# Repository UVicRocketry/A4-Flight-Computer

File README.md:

# Anduril 4 Flight Computer
**Project Charter:** [[[UVR-CH-068] Flight Computer Project Charter]](https://docs.google.com/document/d/1PksAvCCPt7eP-2tlsQyjIq21KkHghG1seeA3lu4UV-o/edit).

## Hardware
Hardware designed in KiCAD. If any footprints are added create a folder with the component name in the component-library folder and export all the files to there. When importing footprints and symbols add them to the A4-Flight-Computer library in KiCAD. Also add any datasheet and relevent documentation to this folder.

## Software
Software is an STM32CubeMX/STM32CubeIDE project using FreeRTOS.
[[Get STM32 software development tools]](https://www.st.com/en/development-tools/stm32-software-development-tools.html)

Unit testing: test infrastructure not set up yet.

### Source organization

The organizational idea is to separate the CubeMX-generated STM32 code from the project-specific application code:

```text
software/A4-Flight-Computer/
├── Core/                         # CubeMX-generated startup and HAL integration
│   ├── Inc/
│   └── Src/
├── App/                          # User-owned flight-computer application
|   ├── Inc/                      # Shared application headers such as config options
|   ├── Src/                      # General application sources such as initialization
│   ├── Services/                 # Services, state machines, etc. shared between tasks
│   ├── Tasks/                    # FreeRTOS task implementations
│   └── Interrupts/               # GPIO/timer/CAN interrupt handlers
├── Drivers/
│   ├── BSP/A4FlightComputer/     # Board-specific hardware abstraction
│   ├── CMSIS/
│   └── STM32H5xx_HAL_Driver/
└── Tests/
    ├── Unit/                     # Google Test unit tests
    └── Mocks/                    # Mock functions for use in unit tests
```

`Core/` should remain mostly as generated by CubeMX. Project-specific application code should be placed in `App/`, hardware interfaces specific to the A4 Flight Computer board
(i.e. accelerometer interface) should be placed in `Drivers/BSP/`, and Google Test cases and mocks should be placed in `Tests/Unit/` and `Tests/Mocks/`.

Handlers in `App/Interrupts/` shall be ISR-safe and perform minimal processing except setting/clearing flags and queuing data to be processed by Tasks. Hardware-independent logic
belongs in `App/Services/` and should not depend directly on STM32 HAL or FreeRTOS.

Unit tests are built on the host with Google Test. Application services
should be testable without STM32 hardware, HAL initialization, or starting the
FreeRTOS scheduler. Use interfaces and fakes for hardware-dependent behavior.

## Setup Guide
*[Fill out if applicable]*

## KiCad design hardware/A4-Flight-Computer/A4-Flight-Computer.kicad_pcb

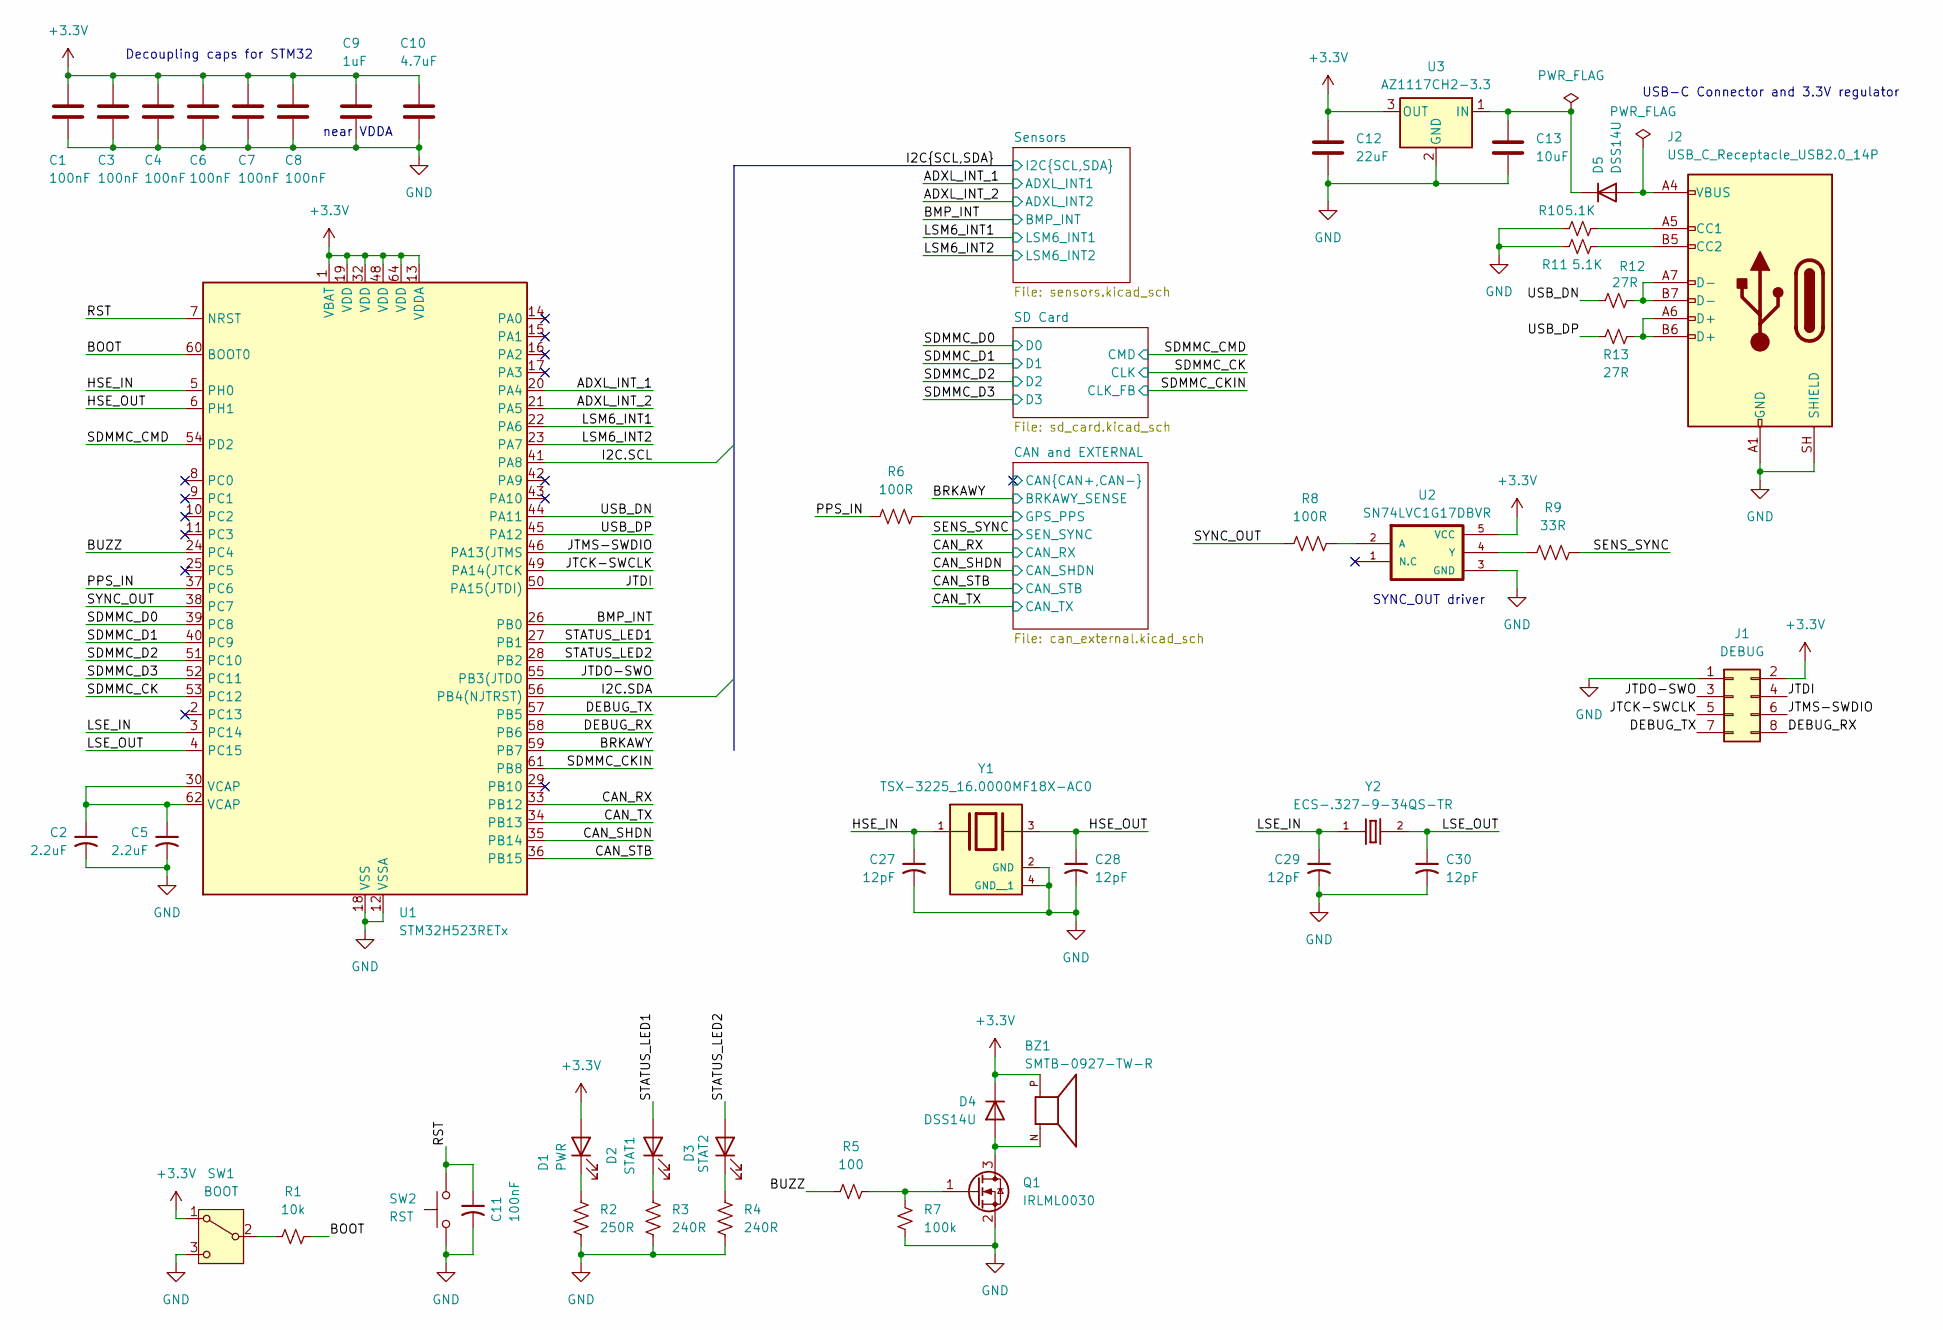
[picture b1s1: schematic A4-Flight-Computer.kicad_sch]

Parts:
BZ1: SMTB-0927-TW-R; XDCR_SMTB-0927-TW-R; MPN SMTB-0927-TW-R
C1, C3, C4, C6, C7, C8, C11: 100nF; C_0402_1005Metric
C2, C5: 2.2uF; C_0402_1005Metric
C9: 1uF; C_0402_1005Metric
C10: 4.7uF; C_0402_1005Metric
C12: 22uF; C_0402_1005Metric
C13: 10uF; C_0402_1005Metric
C27, C28, C29, C30: 12pF; C_0402_1005Metric
D1: PWR; LED_0805_2012Metric
D2: STAT1; LED_0805_2012Metric
D3: STAT2; LED_0805_2012Metric
D4, D5: DSS14U; D_SOD-123
J1: DEBUG; PinHeader_2x04_P2.54mm_Vertical
J2: USB_C_Receptacle_USB2.0_14P; USB_C_Receptacle_Palconn_UTC16-G
Q1: IRLML0030; SOT-23
R1: 10k; R_0402_1005Metric
R2: 250R; R_0402_1005Metric
R3, R4: 240R; R_0402_1005Metric
R5: 100; R_0402_1005Metric
R6, R8: 100R; R_0402_1005Metric
R7: 100k; R_0402_1005Metric
R9: 33R; R_0402_1005Metric
R10, R11: 5.1K; R_0402_1005Metric
R12, R13: 27R; R_0402_1005Metric
SW1: BOOT; SW_SPDT_CK_JS102011SAQN
SW2: RST; SW_SPST_TS-1088-xR025
U1: STM32H523RETx; LQFP-64_10x10mm_P0.5mm
U2: SN74LVC1G17DBVR; SOT95P280X145-5N; MPN SN74LVC1G17DBVR
U3: AZ1117CH2-3.3; SOT-223-3_TabPin2
Y1: TSX-3225_16.0000MF18X-AC0; XTAL_TSX-3225_16.0000MF18X-AC0; MPN TSX-3225 16.0000MF18X-AC0
Y2: ECS-.327-9-34QS-TR; XTAL_ECS-.327-9-34QS-TR; MPN ECS-.327-9-34QS-TR

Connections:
+3.3V: BZ1.P, C1.1, C3.1, C4.1, C6.1, C7.1, C8.1, C9.1, C10.1, C12.1, D1.2 (A), D4.1 (K), J1.2, SW1.1 (A), U1.1 (VBAT), U1.13 (VDDA), U1.19 (VDD), U1.32 (VDD), U1.48 (VDD), U1.64 (VDD), U2.5 (VCC), U3.3 (OUT); also elsewhere on the board
/ADXL_INT_1: U1.20 (PA4); also elsewhere on the board
/ADXL_INT_2: U1.21 (PA5); also elsewhere on the board
/BMP_INT: U1.26 (PB0); also elsewhere on the board
/BOOT: R1.2, U1.60 (BOOT0)
/BRKAWY: U1.59 (PB7); also elsewhere on the board
/BUZZ: R5.1, U1.24 (PC4)
/CAN and EXTERNAL/GPS_PPS: R6.2; also elsewhere on the board
/CAN_RX: U1.33 (PB12); also elsewhere on the board
/CAN_SHDN: U1.35 (PB14); also elsewhere on the board
/CAN_STB: U1.36 (PB15); also elsewhere on the board
/CAN_TX: U1.34 (PB13); also elsewhere on the board
/DEBUG_RX: J1.8, U1.58 (PB6)
/DEBUG_TX: J1.7, U1.57 (PB5)
/HSE_IN: C27.1, U1.5 (PH0), Y1.1
/HSE_OUT: C28.1, U1.6 (PH1), Y1.3
/I2C.SCL: U1.41 (PA8); also elsewhere on the board
/I2C.SDA: U1.56 (PB4(NJTRST)); also elsewhere on the board
/JTCK-SWCLK: J1.5, U1.49 (PA14(JTCK)
/JTDI: J1.4, U1.50 (PA15(JTDI))
/JTDO-SWO: J1.3, U1.55 (PB3(JTDO)
/JTMS-SWDIO: J1.6, U1.46 (PA13(JTMS)
/LSE_IN: C29.1, U1.3 (PC14), Y2.1
/LSE_OUT: C30.1, U1.4 (PC15), Y2.2
/LSM6_INT1: U1.22 (PA6); also elsewhere on the board
/LSM6_INT2: U1.23 (PA7); also elsewhere on the board
/PPS_IN: R6.1, U1.37 (PC6)
/RST: C11.1, SW2.2, U1.7 (NRST)
/SDMMC_CK: U1.53 (PC12); also elsewhere on the board
/SDMMC_CKIN: U1.61 (PB8); also elsewhere on the board
/SDMMC_CMD: U1.54 (PD2); also elsewhere on the board
/SDMMC_D0: U1.39 (PC8); also elsewhere on the board
/SDMMC_D1: U1.40 (PC9); also elsewhere on the board
/SDMMC_D2: U1.51 (PC10); also elsewhere on the board
/SDMMC_D3: U1.52 (PC11); also elsewhere on the board
/SENS_SYNC: R9.2; also elsewhere on the board
/STATUS_LED1: D2.2 (A), U1.27 (PB1)
/STATUS_LED2: D3.2 (A), U1.28 (PB2)
/SYNC_OUT: R8.1, U1.38 (PC7)
/USB_DN: R12.1, U1.44 (PA11)
/USB_DP: R13.1, U1.45 (PA12)
GND: C1.2, C2.2, C3.2, C4.2, C5.2, C6.2, C7.2, C8.2, C9.2, C10.2, C11.2, C12.2, C13.2, C27.2, C28.2, C29.2, C30.2, J1.1, J2.A1 (GND), J2.A12 (GND), J2.B1 (GND), J2.B12 (GND), J2.SH (SHIELD), Q1.2 (S), R2.2, R3.2, R4.2, R7.1, R10.1, R11.1, SW1.3 (C), SW2.1, U1.12 (VSSA), U1.18 (VSS), U1.31 (VSS), U1.47 (VSS), U1.63 (VSS), U2.3 (GND), U3.2 (GND), Y1.2 (GND), Y1.4 (GND__1); also elsewhere on the board
unnamed: C2.1, C5.1, U1.30 (VCAP), U1.62 (VCAP)
unnamed: D1.1 (K), R2.1
unnamed: D2.1 (K), R3.1
unnamed: D3.1 (K), R4.1
unnamed: BZ1.N, D4.2 (A), Q1.3 (D)
unnamed: D5.2 (A), J2.A4 (VBUS), J2.A9 (VBUS), J2.B4 (VBUS), J2.B9 (VBUS)
unnamed: C13.1, D5.1 (K), U3.1 (IN)
unnamed: J2.A5 (CC1), R10.2
unnamed: J2.B5 (CC2), R11.2
unnamed: J2.A6 (D+), J2.B6 (D+), R13.2
unnamed: J2.A7 (D-), J2.B7 (D-), R12.2
unnamed: Q1.1 (G), R5.2, R7.2
unnamed: R1.1, SW1.2 (B)
unnamed: R8.2, U2.2 (A)
unnamed: R9.1, U2.4 (Y)

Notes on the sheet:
Decoupling caps for STM32
USB-C Connector and 3.3V regulator
SYNC_OUT driver
near VDDA

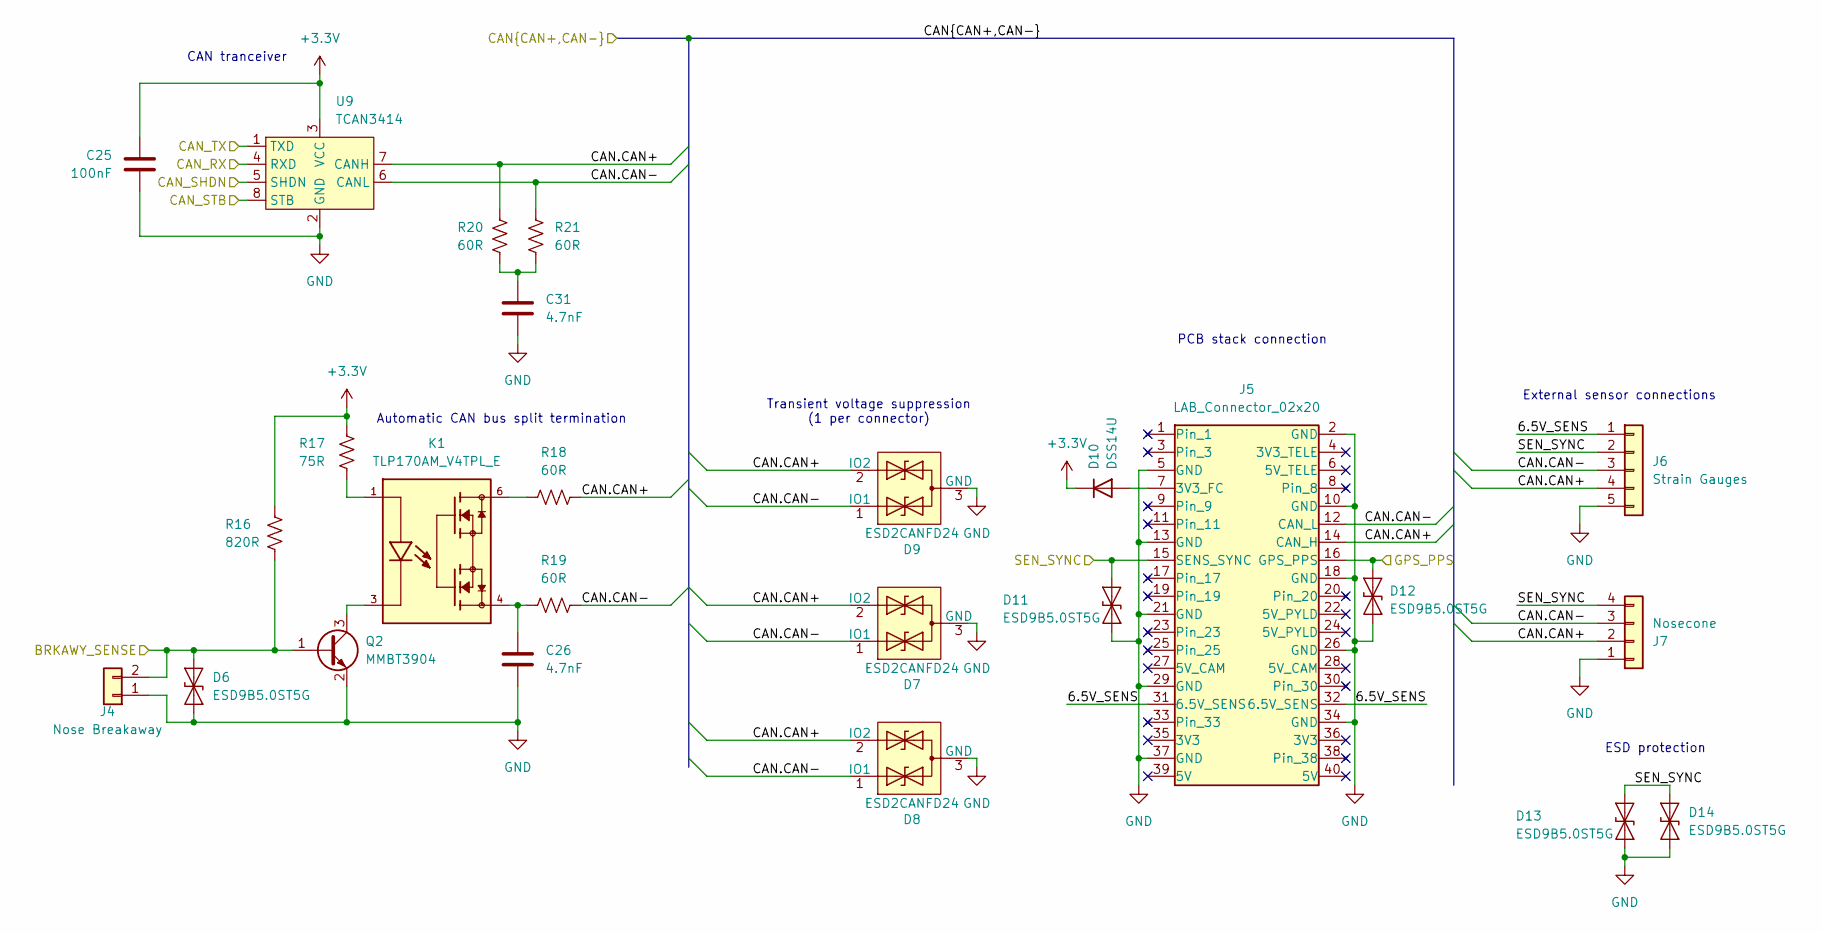
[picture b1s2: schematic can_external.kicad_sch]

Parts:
C25: 100nF; C_0402_1005Metric
C26, C31: 4.7nF; C_0402_1005Metric
D6, D11, D12, D13, D14: ESD9B5.0ST5G; D_SOD-923
D7, D8, D9: ESD2CANFD24; ESD2CANFD24-SOT23
D10: DSS14U; D_SOD-123
J4: Nose Breakaway; JST_XH_S2B-XH-A_1x02_P2.50mm_Horizontal
J5: LAB_Connector_02x20; LAB_PCB_With_Header
J6: Strain Gauges; JST_XH_S5B-XH-A_1x05_P2.50mm_Horizontal
J7: Nosecone; JST_XH_S4B-XH-A_1x04_P2.50mm_Horizontal
K1: TLP170AM_V4TPL_E; RELAY_TLP170AM_V4TPL_E; MPN TLP170AM(V4TPL,E
Q2: MMBT3904; SOT-23
R16: 820R; R_0402_1005Metric
R17: 75R; R_0402_1005Metric
R18, R19, R20, R21: 60R; R_0402_1005Metric
U9: TCAN3414; TCAN3414DR-SOIC8

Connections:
+3.3V: C25.1, D10.1 (K), R16.1, R17.1, U9.3 (VCC); also elsewhere on the board
/BRKAWY: D6.2 (A2), J4.2, Q2.1 (B), R16.2; also elsewhere on the board
/CAN and EXTERNAL/6.5V_SENS: J5.31 (6.5V_SENS), J5.32 (6.5V_SENS), J6.1
/CAN and EXTERNAL/CAN.CAN+: D7.2 (IO2), D8.2 (IO2), D9.2 (IO2), J5.14 (CAN_H), J6.4, J7.2, R18.2, R20.2, U9.7 (CANH)
/CAN and EXTERNAL/CAN.CAN-: D7.1 (IO1), D8.1 (IO1), D9.1 (IO1), J5.12 (CAN_L), J6.3, J7.3, R19.2, R21.2, U9.6 (CANL)
/CAN and EXTERNAL/GPS_PPS: D12.2 (A2), J5.16 (GPS_PPS); also elsewhere on the board
/CAN_RX: U9.4 (RXD); also elsewhere on the board
/CAN_SHDN: U9.5 (SHDN); also elsewhere on the board
/CAN_STB: U9.8 (STB); also elsewhere on the board
/CAN_TX: U9.1 (TXD); also elsewhere on the board
/SENS_SYNC: D11.2 (A2), D13.2 (A2), D14.2 (A2), J5.15 (SENS_SYNC), J6.2, J7.4; also elsewhere on the board
GND: C25.2, C26.2, C31.2, D6.1 (A1), D7.3 (GND), D8.3 (GND), D9.3 (GND), D11.1 (A1), D12.1 (A1), D13.1 (A1), D14.1 (A1), J4.1, J5.2 (GND), J5.5 (GND), J5.10 (GND), J5.13 (GND), J5.18 (GND), J5.21 (GND), J5.26 (GND), J5.29 (GND), J5.34 (GND), J5.37 (GND), J6.5, J7.1, Q2.2 (E), U9.2 (GND); also elsewhere on the board
unnamed: C26.1, K1.4, R19.1
unnamed: C31.1, R20.1, R21.1
unnamed: D10.2 (A), J5.7 (3V3_FC)
unnamed: K1.1, R17.2
unnamed: K1.6, R18.1
unnamed: K1.3, Q2.3 (C)

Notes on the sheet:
CAN tranceiver
Transient voltage suppression (1 per connector)
PCB stack connection
ESD protection
Automatic CAN bus split termination
External sensor connections

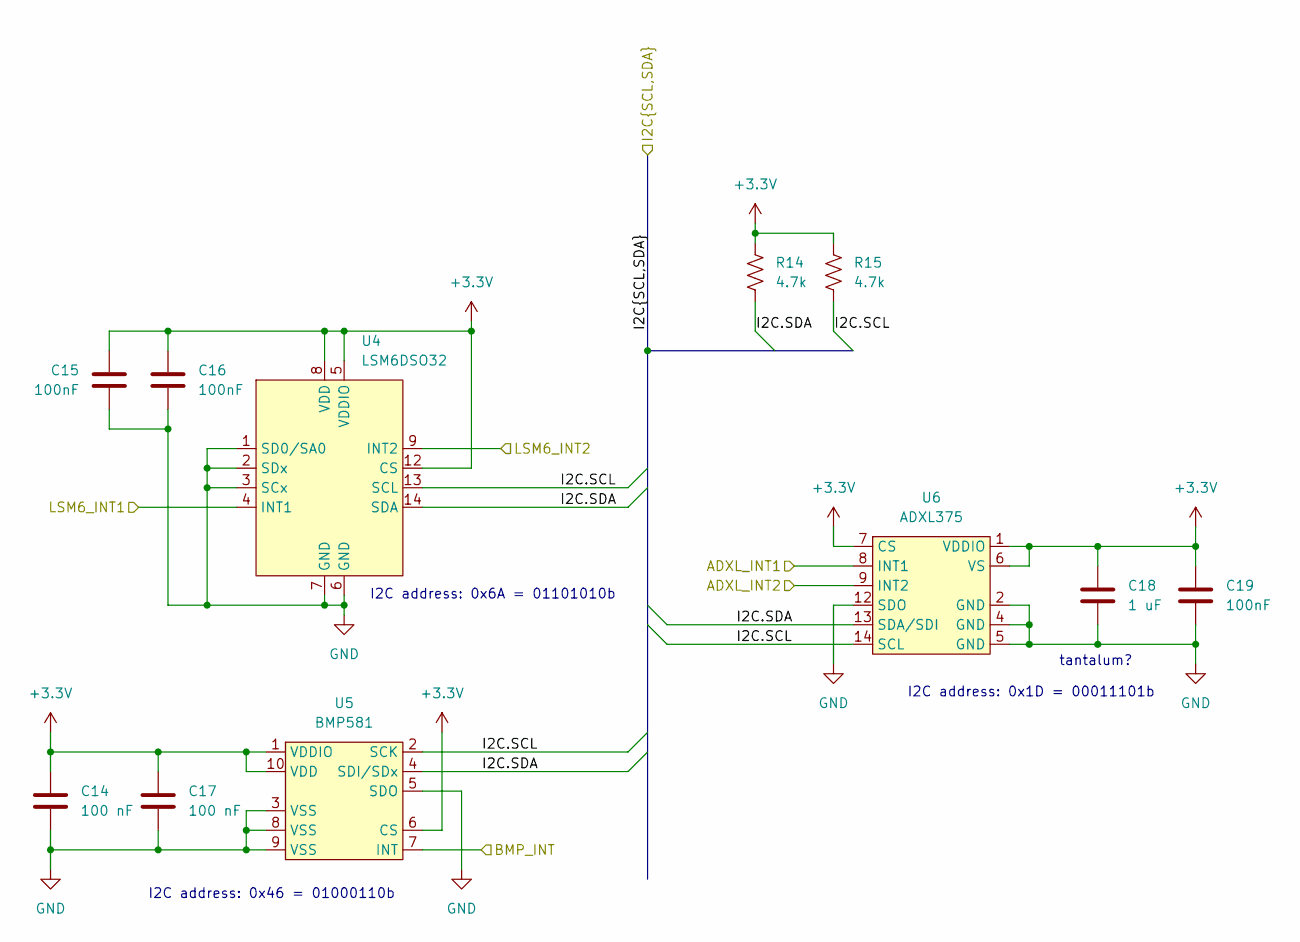
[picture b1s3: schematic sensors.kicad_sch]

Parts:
C14, C17: 100 nF; C_0402_1005Metric
C15, C16, C19: 100nF; C_0402_1005Metric
C18: 1 uF; C_0402_1005Metric
R14, R15: 4.7k; R_0402_1005Metric
U4: LSM6DSO32; LGA-14_3x2.5mm_P0.5mm_LayoutBorder3x4y
U5: BMP581
U6: ADXL375; ADXL375-LGA14

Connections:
+3.3V: C14.1, C15.1, C16.1, C17.1, C18.1, C19.1, R14.1, R15.1, U4.5 (VDDIO), U4.8 (VDD), U4.12 (CS), U5.1 (VDDIO), U5.6 (CS), U5.10 (VDD), U6.1 (VDDIO), U6.6 (VS), U6.7 (CS); also elsewhere on the board
/ADXL_INT_1: U6.8 (INT1); also elsewhere on the board
/ADXL_INT_2: U6.9 (INT2); also elsewhere on the board
/BMP_INT: U5.7 (INT); also elsewhere on the board
/I2C.SCL: R15.2, U4.13 (SCL), U5.2 (SCK), U6.14 (SCL); also elsewhere on the board
/I2C.SDA: R14.2, U4.14 (SDA), U5.4 (SDI/SDx), U6.13 (SDA/SDI); also elsewhere on the board
/LSM6_INT1: U4.4 (INT1); also elsewhere on the board
/LSM6_INT2: U4.9 (INT2); also elsewhere on the board
GND: C14.2, C15.2, C16.2, C17.2, C18.2, C19.2, U4.1 (SD0/SA0), U4.2 (SDx), U4.3 (SCx), U4.6 (GND), U4.7 (GND), U5.3 (VSS), U5.5 (SDO), U5.8 (VSS), U5.9 (VSS), U6.2 (GND), U6.4 (GND), U6.5 (GND), U6.12 (SDO); also elsewhere on the board

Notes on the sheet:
tantalum?
I2C address: 0x46 = 01000110b
I2C address: 0x1D = 00011101b
I2C address: 0x6A = 01101010b

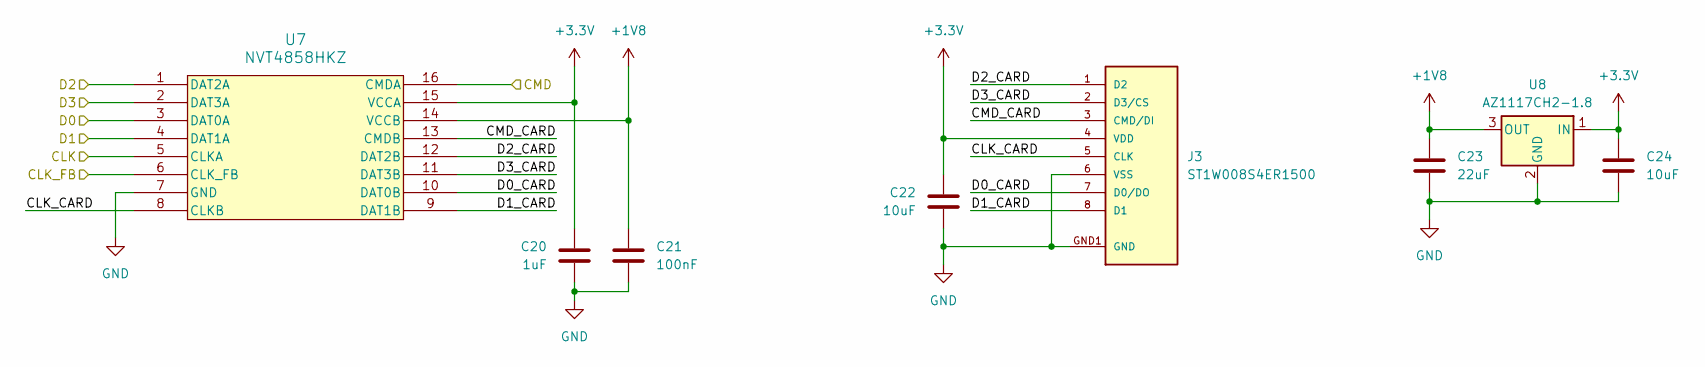
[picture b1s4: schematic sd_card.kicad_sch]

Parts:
C20: 1uF; C_0402_1005Metric
C21: 100nF; C_0402_1005Metric
C22, C24: 10uF; C_0402_1005Metric
C23: 22uF; C_0402_1005Metric
J3: ST1W008S4ER1500; JAE_ST1W008S4ER1500; PARTREV 2; DigiKey_Part_Number 670-1528-1-ND
U7: NVT4858HKZ; NVT4858_NXP-L
U8: AZ1117CH2-1.8; SOT-223-3_TabPin2

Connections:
+1V8: C21.1, C23.1, U7.14 (VCCB), U8.3 (OUT)
+3.3V: C20.1, C22.1, C24.1, J3.4 (VDD), U7.15 (VCCA), U8.1 (IN); also elsewhere on the board
/SD Card/CLK_CARD: J3.5 (CLK), U7.8 (CLKB)
/SD Card/CMD_CARD: J3.3 (CMD/DI), U7.13 (CMDB)
/SD Card/D0_CARD: J3.7 (D0/DO), U7.10 (DAT0B)
/SD Card/D1_CARD: J3.8 (D1), U7.9 (DAT1B)
/SD Card/D2_CARD: J3.1 (D2), U7.12 (DAT2B)
/SD Card/D3_CARD: J3.2 (D3/CS), U7.11 (DAT3B)
/SDMMC_CK: U7.5 (CLKA); also elsewhere on the board
/SDMMC_CKIN: U7.6 (CLK_FB); also elsewhere on the board
/SDMMC_CMD: U7.16 (CMDA); also elsewhere on the board
/SDMMC_D0: U7.3 (DAT0A); also elsewhere on the board
/SDMMC_D1: U7.4 (DAT1A); also elsewhere on the board
/SDMMC_D2: U7.1 (DAT2A); also elsewhere on the board
/SDMMC_D3: U7.2 (DAT3A); also elsewhere on the board
GND: C20.2, C21.2, C22.2, C23.2, C24.2, J3.6 (VSS), J3.GND1 (GND), J3.GND2 (GND), J3.GND3 (GND), J3.GND4 (GND), U7.7 (GND), U8.2 (GND); also elsewhere on the board

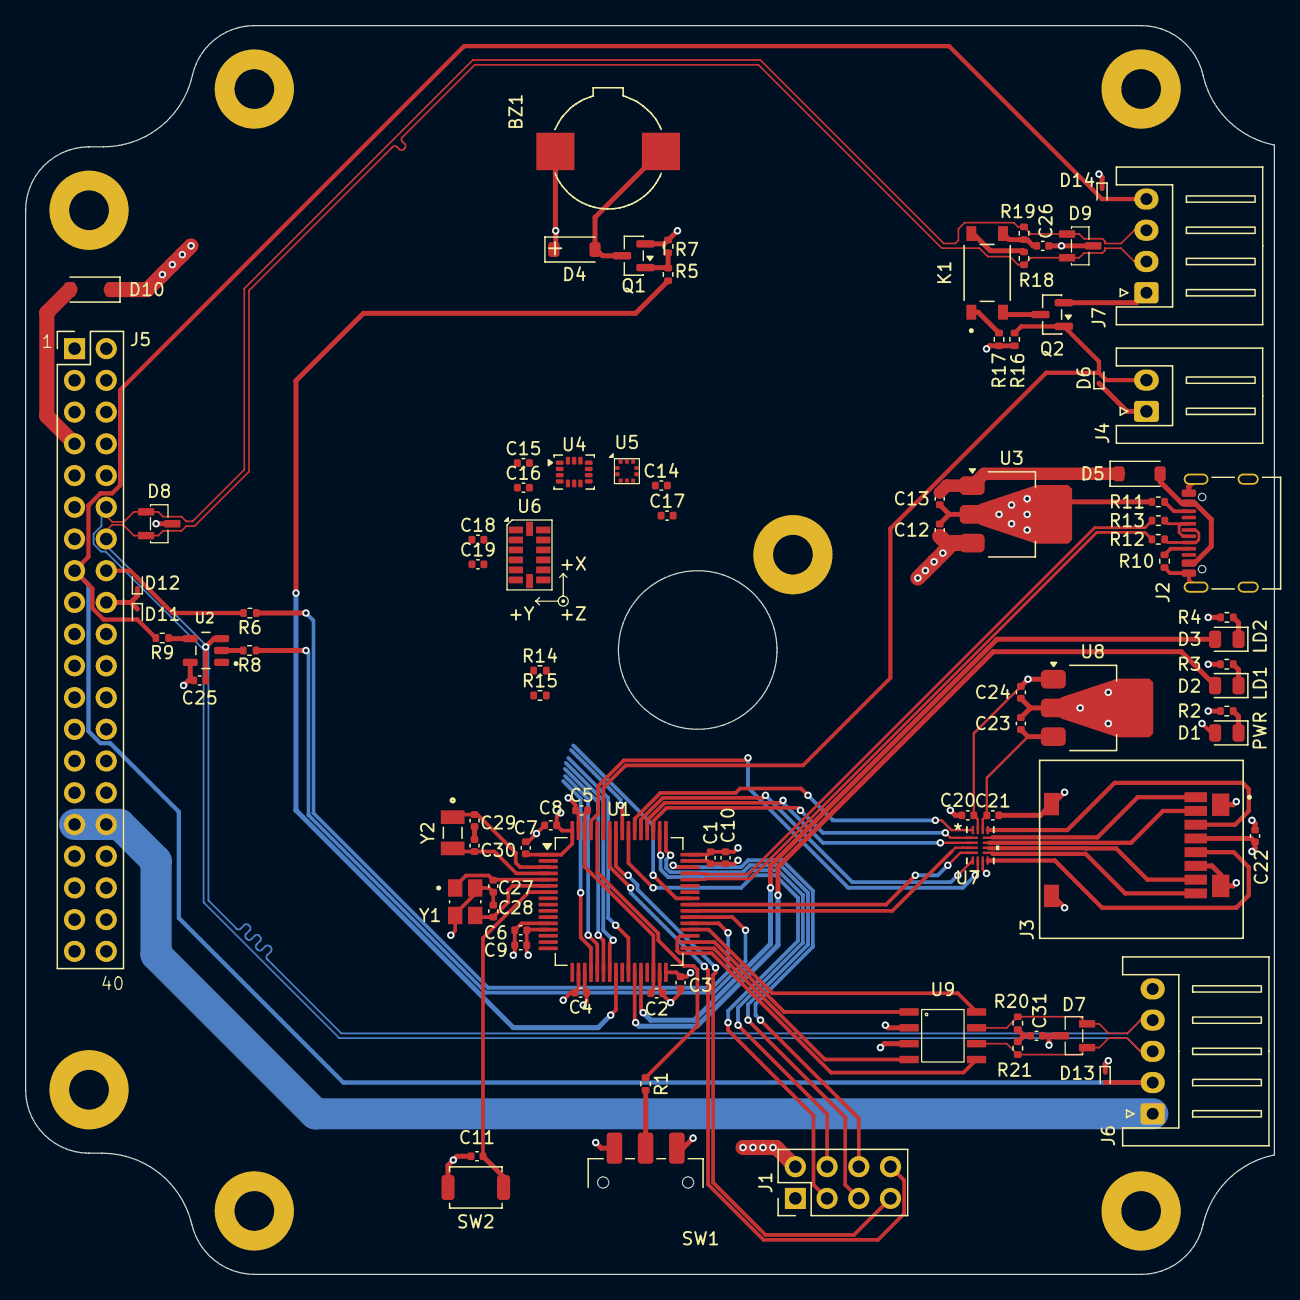
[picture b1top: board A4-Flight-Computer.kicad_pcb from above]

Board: 4 copper layers, 100.0 x 100.0 mm, 90 parts (0 on the bottom side), 73 nets.

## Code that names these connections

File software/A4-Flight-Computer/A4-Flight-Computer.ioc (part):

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Mcu.Name=STM32H523RETx
Mcu.Package=LQFP64
Mcu.UserName=STM32H523RETx
PA11.Mode=Device
PA11.Signal=USB_DM
PA12.Mode=Device
PA12.Signal=USB_DP
PA13(JTMS/SWDIO).Mode=JTAG_4_pins
PA13(JTMS/SWDIO).Signal=DEBUG_JTMS-SWDIO
PA14(JTCK/SWCLK).Mode=JTAG_4_pins
PA14(JTCK/SWCLK).Signal=DEBUG_JTCK-SWCLK
PA15(JTDI).Mode=JTAG_4_pins
PA15(JTDI).Signal=DEBUG_JTDI
PA4.GPIOParameters=GPIO_Label
PA4.GPIO_Label=ADXL_INT1
PA4.Signal=GPXTI4
PA5.GPIOParameters=GPIO_Label
PA5.GPIO_Label=ADXL_INT2
PA5.Signal=GPXTI5
PA6.GPIOParameters=GPIO_Label
PA6.GPIO_Label=LSM6_INT1
PA6.Signal=GPXTI6
PA7.GPIOParameters=GPIO_Label
PA7.GPIO_Label=LSM6_INT2
PA7.Signal=GPXTI7
PA8.Mode=I2C
PA8.Signal=I2C3_SCL
PB0.GPIOParameters=GPIO_Label
PB0.GPIO_Label=BMP_INT
PB0.Signal=GPXTI0
PB1.GPIOParameters=GPIO_Label
PB1.GPIO_Label=LED1
PB1.Signal=GPIO_Output
PB10.GPIOParameters=GPIO_Label
PB10.GPIO_Label=BRKWAY_SENSE
PB10.Signal=GPXTI10
PB12.Mode=FDCAN_Activate
PB12.Signal=FDCAN2_RX
PB13.Mode=FDCAN_Activate
PB13.Signal=FDCAN2_TX
PB14.GPIOParameters=GPIO_Label
PB14.GPIO_Label=CAN_SHDN
PB14.Signal=GPIO_Output
PB15.GPIOParameters=GPIO_Label
PB15.GPIO_Label=CAN_STB
PB15.Signal=GPIO_Output
PB2.GPIOParameters=GPIO_Label
PB2.GPIO_Label=LED2
PB2.Signal=GPIO_Output
PB3(JTDO/TRACESWO).Mode=JTAG_4_pins
PB3(JTDO/TRACESWO).Signal=DEBUG_JTDO-SWO
PB4(NJTRST).Mode=I2C
PB4(NJTRST).Signal=I2C3_SDA
PB5.Mode=Asynchronous
PB5.Signal=USART6_TX
PB6.Mode=Asynchronous
PB6.Signal=USART6_RX
PB8.Mode=SD_4_bits_Wide_bus_auto_dir_voltage_converter
PB8.Signal=SDMMC1_CKIN
PC10.Mode=SD_4_bits_Wide_bus_auto_dir_voltage_converter
PC10.Signal=SDMMC1_D2
PC11.Mode=SD_4_bits_Wide_bus_auto_dir_voltage_converter
PC11.Signal=SDMMC1_D3
PC12.Mode=SD_4_bits_Wide_bus_auto_dir_voltage_converter
PC12.Signal=SDMMC1_CK
PC14-OSC32_IN(OSC32_IN).Mode=LSE-External-Oscillator
PC14-OSC32_IN(OSC32_IN).Signal=RCC_OSC32_IN
PC15-OSC32_OUT(OSC32_OUT).Mode=LSE-External-Oscillator
PC15-OSC32_OUT(OSC32_OUT).Signal=RCC_OSC32_OUT
PC4.GPIOParameters=GPIO_Label
PC4.GPIO_Label=BUZZ_OUT
PC4.Signal=S_TIM2_CH4
PC6.GPIOParameters=GPIO_PuPd,GPIO_Label
PC6.GPIO_Label=PPS_IN
PC6.GPIO_PuPd=GPIO_PULLDOWN
PC6.Signal=S_TIM3_CH1
PC7.GPIOParameters=GPIO_Speed,GPIO_Label
PC7.GPIO_Label=SYNC_OUT
PC7.GPIO_Speed=GPIO_SPEED_FREQ_MEDIUM
PC7.Signal=S_TIM3_CH2
PC8.Mode=SD_4_bits_Wide_bus_auto_dir_voltage_converter
PC8.Signal=SDMMC1_D0
PC9.Mode=SD_4_bits_Wide_bus_auto_dir_voltage_converter
PC9.Signal=SDMMC1_D1
PD2.Mode=SD_4_bits_Wide_bus_auto_dir_voltage_converter
PD2.Signal=SDMMC1_CMD
PH0-OSC_IN(PH0).Mode=HSE-External-Oscillator
PH0-OSC_IN(PH0).Signal=RCC_OSC_IN
PH1-OSC_OUT(PH1).Mode=HSE-External-Oscillator
PH1-OSC_OUT(PH1).Signal=RCC_OSC_OUT
RCC.HSE_VALUE=16000000
RCC.SYSCLKFreq_VALUE=240000000
RCC.SYSCLKSource=RCC_SYSCLKSOURCE_PLLCLK
board=custom
